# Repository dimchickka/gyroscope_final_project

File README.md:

Gyroscope Data Logger (STM32F103C8T6)
Overview
This project is an autonomous data logging device built around the STM32F103C8T6 (Blue Pill) microcontroller. It reads real-time data from a gyroscope sensor and saves the logs directly onto an SD card. The device is designed for portability, powered by a LiPo battery featuring convenient USB charging.

Photo Gallery
<div align="center">

</div>

<div align="center">

<p><em>The fully assembled Gyroscope Data Logger.</em></p>
</div>

🚀 Key Features
Microcontroller: STM32F103C8T6 (Cortex-M3).

Sensor: High-precision Gyroscope (interfaced via I2C).

Data Storage: Reliable data logging to a MicroSD card

Power System: Portable LiPo battery operation with an integrated USB charging circuit.

Communication Interfaces:

SPI: Used for high-speed communication with the SD card module.

I2C: Used for retrieving sensor data from the gyroscope.

UART: Available for debugging purposes.

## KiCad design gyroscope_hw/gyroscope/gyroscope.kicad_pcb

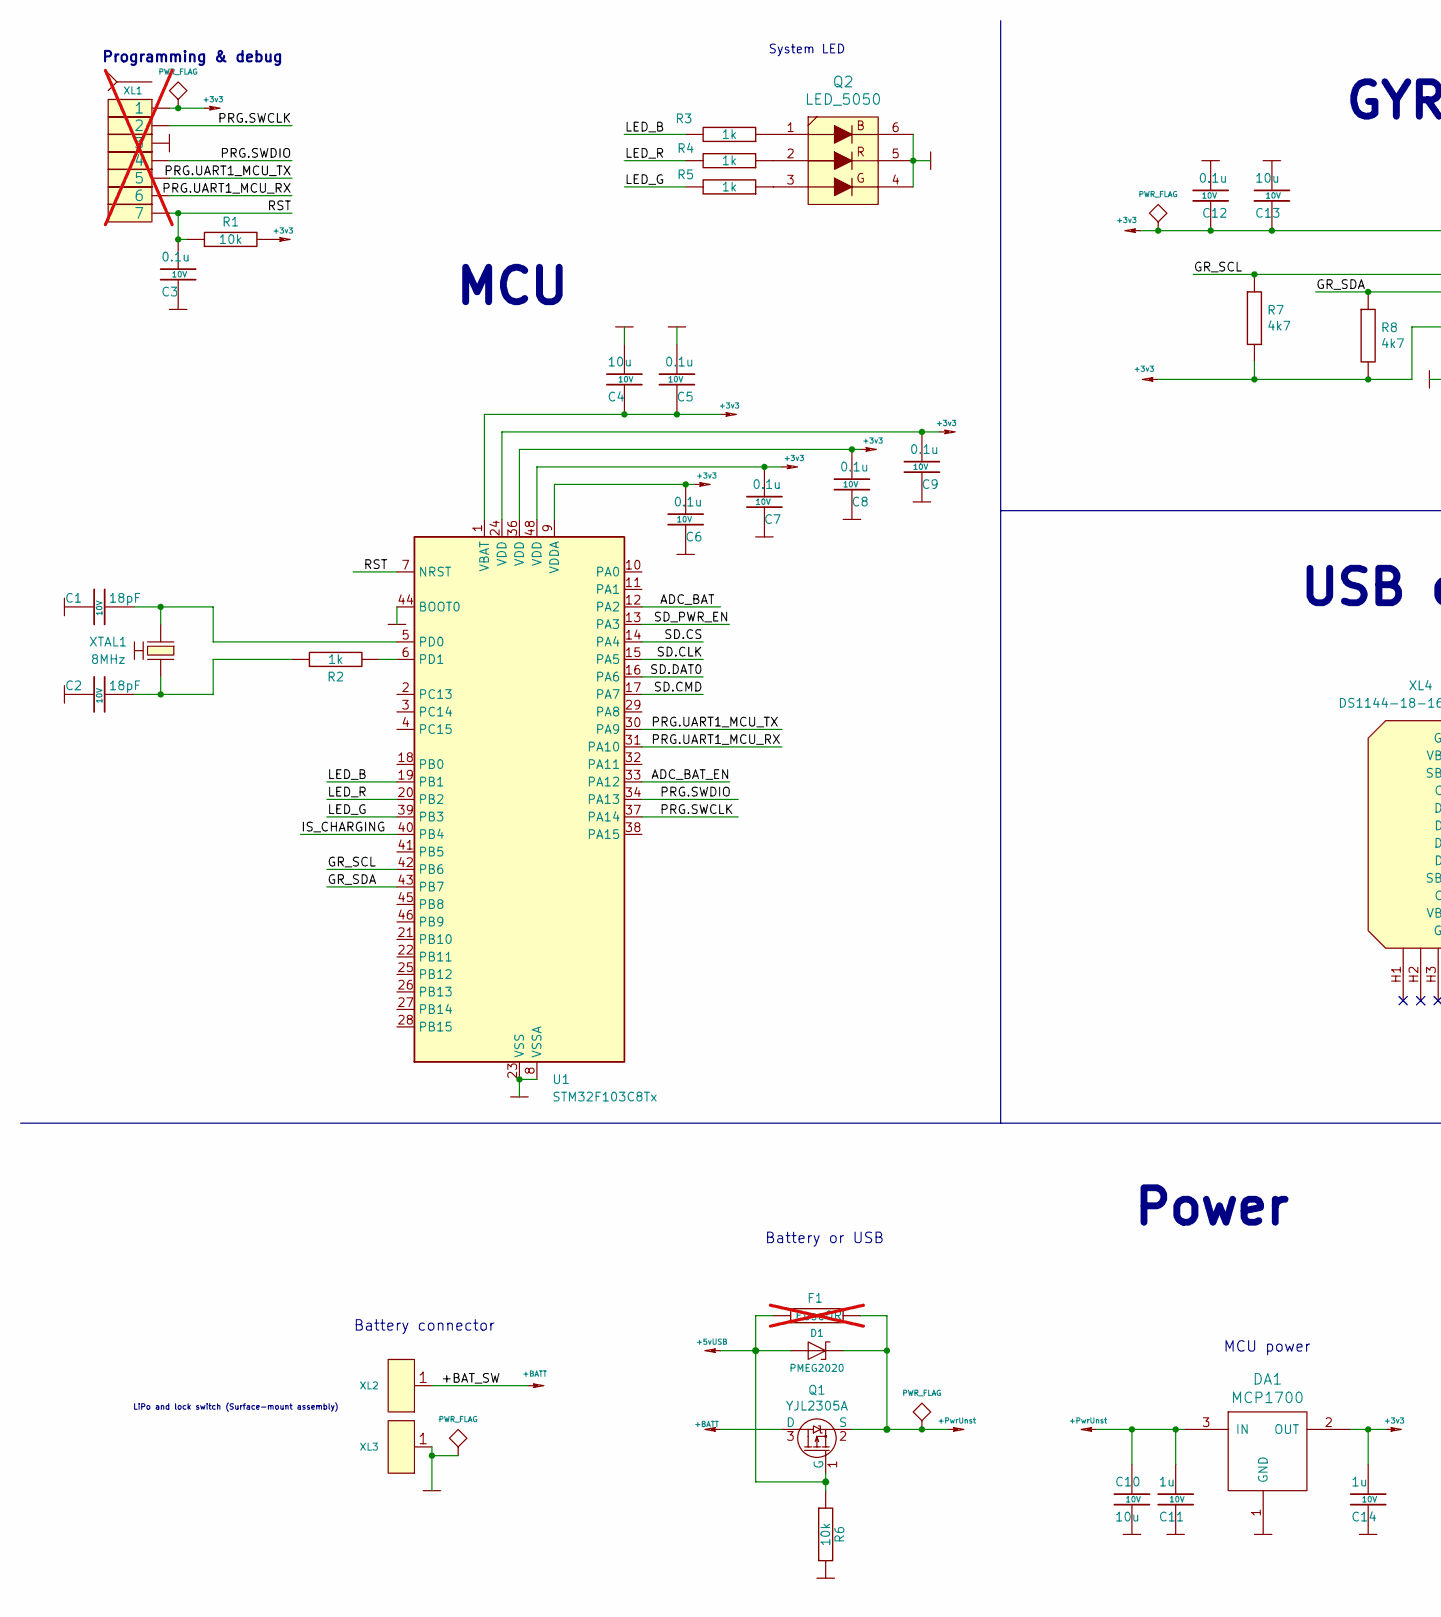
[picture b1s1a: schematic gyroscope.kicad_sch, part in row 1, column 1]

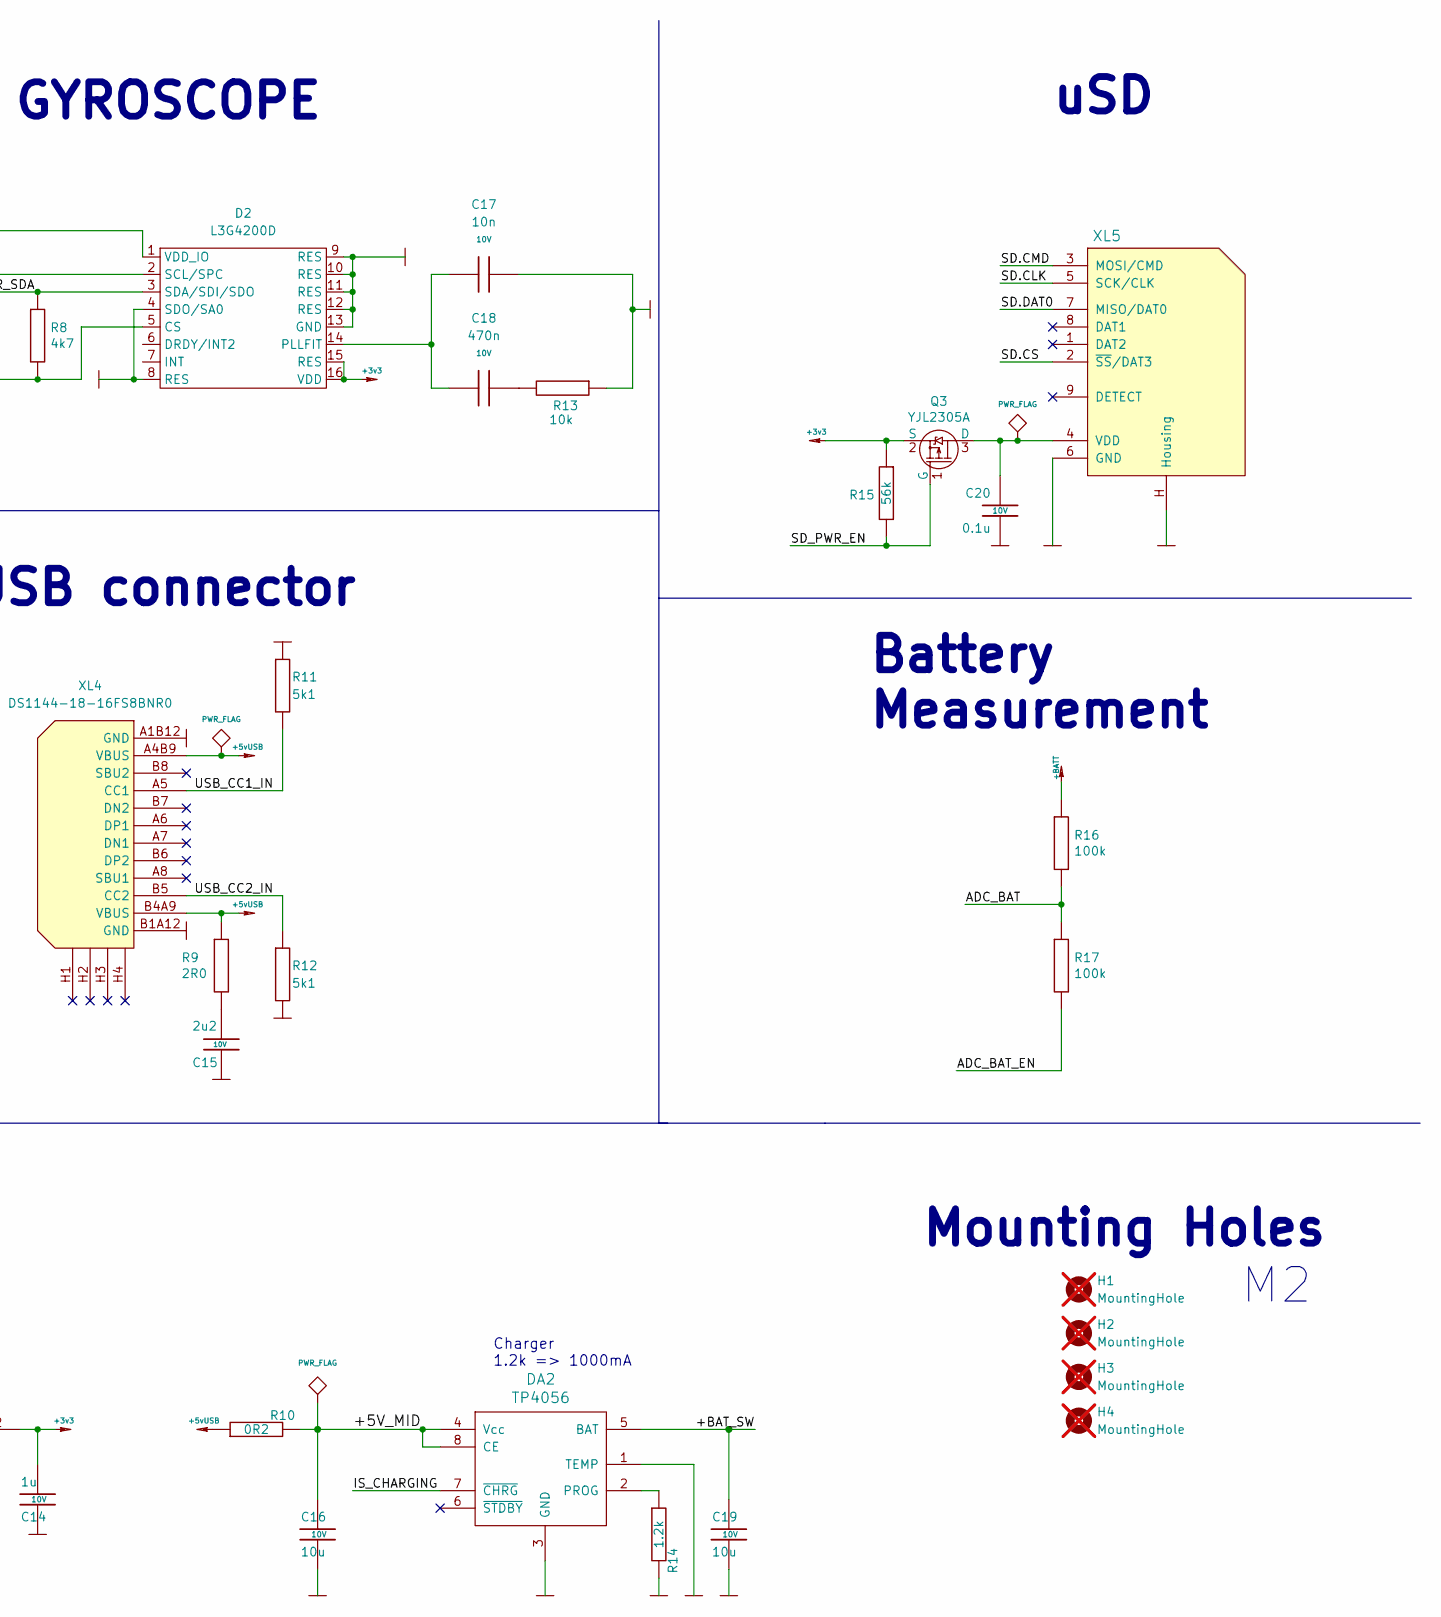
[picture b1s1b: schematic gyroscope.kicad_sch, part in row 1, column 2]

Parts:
C1, C2: 18pF; CAP_0603_Silks; Tolerance 20%; Voltage 10V
C3, C5, C6, C7, C8, C9, C12: 0.1u; CAP_0603_Silks; Tolerance 20%; Voltage 10V
C4, C10, C13, C16, C19: 10u; CAP_0603_Silks; Tolerance 20%; Voltage 10V
C11, C14: 1u; CAP_0603_Silks; Tolerance 20%; Voltage 10V
C15: 2u2; CAP_0603_Silks; Tolerance 20%; Voltage 10V
C17: 10n; CAP_0603_Silks; Tolerance 20%; Voltage 10V
C18: 470n; CAP_0603_Silks; Tolerance 20%; Voltage 10V
C20: 0.1u; CAP_0603_Silks; Voltage 10V; Tolerance 20%
D1: PMEG2020; SOD323
D2: L3G4200D; LGA-16_4x4mm_P0.65mm_LayoutBorder4x4y
DA1: MCP1700; SOT23-3A
DA2: TP4056; SO8_150MIL
F1: Fuse0R; RES_0603_FUSE; not fitted
H1, H2, H3, H4: MountingHole; MountingHole_2.2mm_M2; not fitted
Q1, Q3: YJL2305A; SOT23-3
Q2: LED_5050
R1, R6, R13: 10k; RES_0603_Silks; Tolerance 1%
R2, R3, R4, R5: 1k; RES_0603_Silks; Tolerance 1%
R7, R8: 4k7; RES_0603_Silks; Tolerance 1%
R9: 2R0; RES_0603_Silks; Tolerance 1%
R10: 0R2; RES_1206; Tolerance 1%
R11, R12: 5k1; RES_0603_Silks; Tolerance 1%
R14: 1.2k; RES_0603_Silks; Tolerance 1%
R15: 56k; RES_0603_Silks; Tolerance 1%
R16, R17: 100k; RES_0603_Silks; Tolerance 1%
U1: STM32F103C8Tx; LQFP-48_7x7mm_P0.5mm
XL1: SOCKET_7; PLS-7_LOCK; not fitted
XL2: CONN_1; Round_1MM5
XL3: CONN_1; Square_1MM5
XL4: DS1144-18-16FS8BNR0; USBC_DS1144-18
XL5: CONN_MICROSD; MICROSD_EJECTOR_TFWF1
XTAL1: 8MHz; 03225C4

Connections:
+3v3: C4.2, C5.2, C6.1, C7.1, C8.1, C9.1, C12.2, C13.2, C14.1, D2.1 (VDD_IO), D2.5 (CS), D2.15 (RES), D2.16 (VDD), DA1.2 (OUT), Q3.2 (S), R1.2, R7.2, R8.2, R15.1, U1.1 (VBAT), U1.9 (VDDA), U1.24 (VDD), U1.36 (VDD), U1.48 (VDD), XL1.1
+5vUSB: D1.A, F1.1, Q1.1 (G), R6.1, R9.1, R10.1, XL4.A4B9 (VBUS), XL4.B4A9 (VBUS)
+BATT: C19.2, DA2.5 (BAT), Q1.3 (D), R16.1, XL2.1
+PwrUnst: C10.2, C11.1, D1.C, DA1.3 (IN), F1.2, Q1.2 (S)
/+5V_MID: C16.2, DA2.4 (Vcc), DA2.8 (CE), R10.2
/ADC_BAT: R16.2, R17.1, U1.12 (PA2)
/ADC_BAT_EN: R17.2, U1.33 (PA12)
/GR_SCL: D2.2 (SCL/SPC), R7.1, U1.42 (PB6)
/GR_SDA: D2.3 (SDA/SDI/SDO), R8.1, U1.43 (PB7)
/IS_CHARGING: DA2.7 (~CHRG), U1.40 (PB4)
/LED_B: R3.2, U1.19 (PB1)
/LED_G: R5.2, U1.39 (PB3)
/LED_R: R4.2, U1.20 (PB2)
/PRG.SWCLK: U1.37 (PA14), XL1.2
/PRG.SWDIO: U1.34 (PA13), XL1.4
/PRG.UART1_MCU_RX: U1.31 (PA10), XL1.6
/PRG.UART1_MCU_TX: U1.30 (PA9), XL1.5
/RST: C3.1, R1.1, U1.7 (NRST), XL1.7
/SD.CLK: U1.15 (PA5), XL5.5 (SCK/CLK)
/SD.CMD: U1.17 (PA7), XL5.3 (MOSI/CMD)
/SD.CS: U1.14 (PA4), XL5.2 (~SS/DAT3)
/SD.DAT0: U1.16 (PA6), XL5.7 (MISO/DAT0)
/SD_PWR_EN: Q3.1 (G), R15.2, U1.13 (PA3)
/USB_CC1_IN: R11.2, XL4.A5 (CC1)
/USB_CC2_IN: R12.1, XL4.B5 (CC2)
GND: C1.2, C2.2, C3.2, C4.1, C5.1, C6.2, C7.2, C8.2, C9.2, C10.1, C11.2, C12.1, C13.1, C14.2, C15.2, C16.1, C17.2, C19.1, C20.2, D2.4 (SDO/SA0), D2.8 (RES), D2.9 (RES), D2.10 (RES), D2.11 (RES), D2.12 (RES), D2.13 (GND), DA1.1 (GND), DA2.1 (TEMP), DA2.3 (GND), Q2.4 (B), Q2.5 (G), Q2.6, R6.2, R11.1, R12.2, R13.1, R14.2, U1.8 (VSSA), U1.23 (VSS), U1.35 (VSS), U1.44 (BOOT0), U1.47 (VSS), XL1.3, XL3.1, XL4.A1B12 (GND), XL4.B1A12 (GND), XL5.6 (GND), XL5.H (Housing), XTAL1.H
unnamed: C2.1, R2.1, XTAL1.2
unnamed: C15.1, R9.2
unnamed: C18.2, R13.2
unnamed: C17.1, C18.1, D2.14 (PLLFIT)
unnamed: DA2.2 (PROG), R14.1
unnamed: Q2.1, R3.1
unnamed: Q2.2, R4.1
unnamed: Q2.3, R5.1
unnamed: C20.1, Q3.3 (D), XL5.4 (VDD)
unnamed: C1.1, U1.5 (PD0), XTAL1.1
unnamed: R2.2, U1.6 (PD1)

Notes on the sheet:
Charger 1.2k => 1000mA
Battery connector
MCU
MCU power
Power
USB connector
Battery Measurement
LiPo and lock switch (Surface-mount assembly)
Mounting Holes
GYROSCOPE
Battery or USB
Programming & debug
System LED
uSD

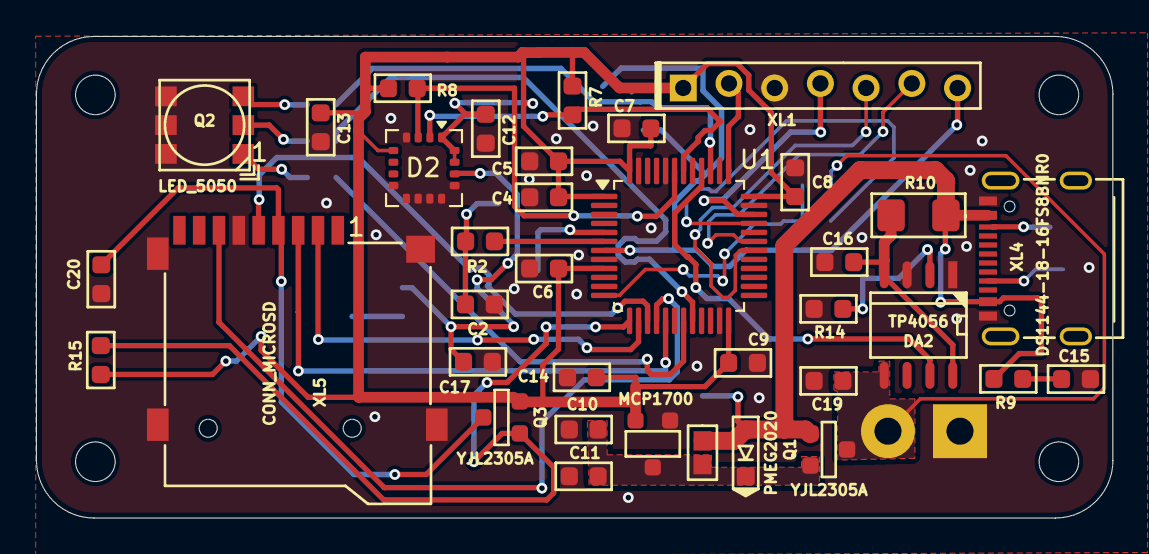
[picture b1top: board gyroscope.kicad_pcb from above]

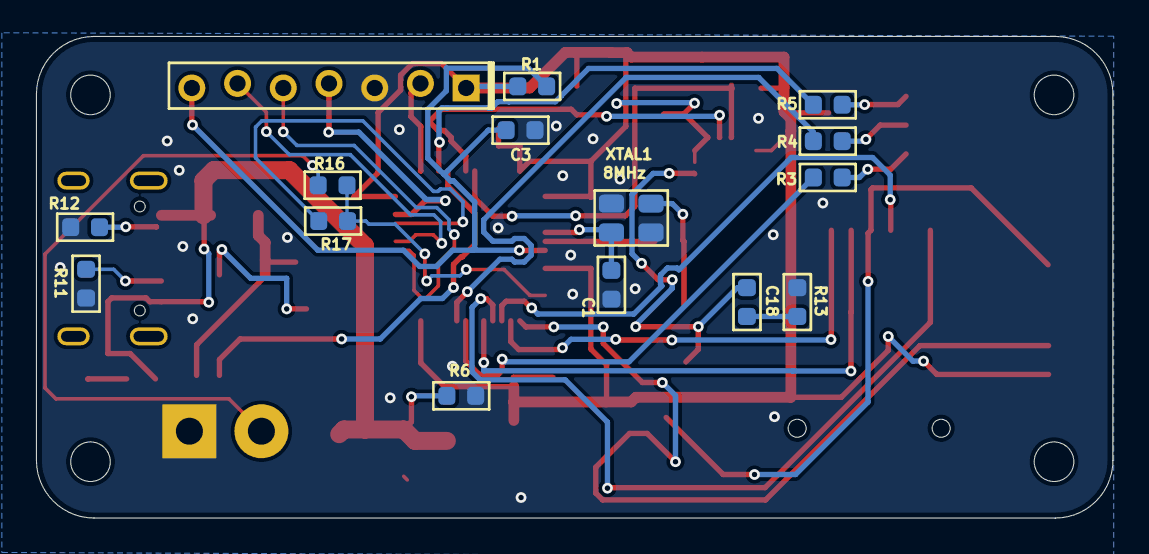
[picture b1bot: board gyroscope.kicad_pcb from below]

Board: 2 copper layers, 59.8 x 26.8 mm, 56 parts (16 on the bottom side), 37 nets.

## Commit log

2026-04-07 Added firmware and correct PCB
2026-04-07 add photo
